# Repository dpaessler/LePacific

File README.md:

# LePacific

RIAA MM JFET Phono Preamplifier based on the design found here:

http://diyaudioprojects.com/Solid/JFET-Phono-Preamplifier-Kit/diy-jfet-riaa-phono-preamp.html

An additional EAGLE library is used for the JFET, which can be found here:

http://www.diymodules.org/eagle-show-library?type=usr&id=3220&part=toshiba-jfet.lbr

The coupling capacitors have to be added separately, they don't fit on the board. I used a matched pair
of NOS russian military 2.2uF 250V PIO capacitors K75-10.

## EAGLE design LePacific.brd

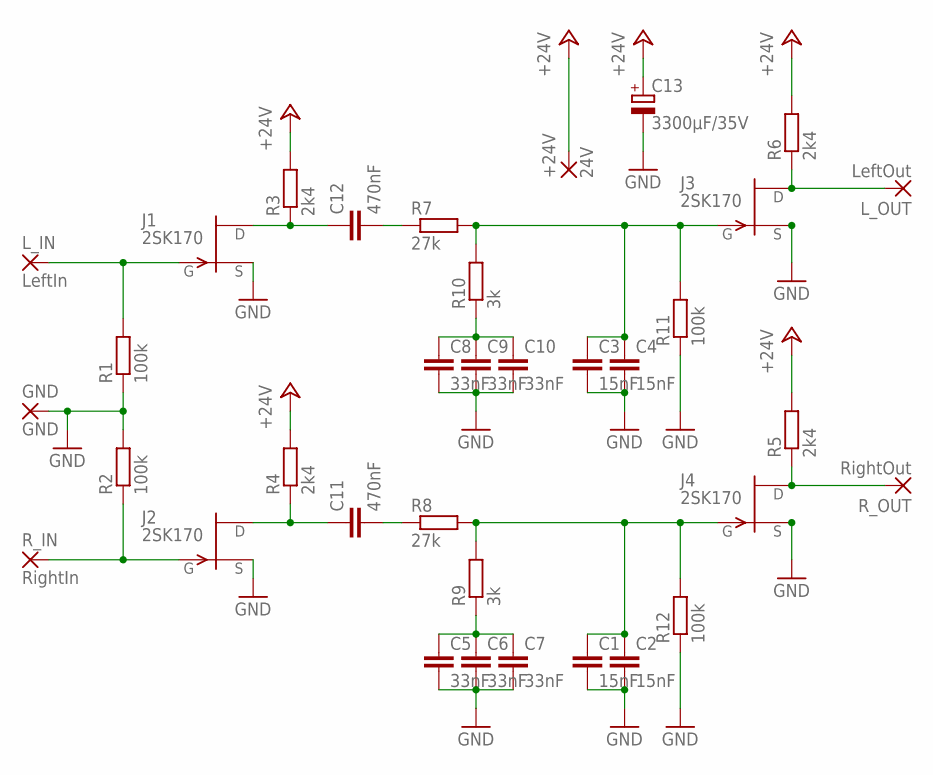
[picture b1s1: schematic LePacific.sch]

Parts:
+24V: 24V; 2,54/0,8
C1, C2, C3, C4: 15nF; C150-054X183
C5, C6, C7, C8, C9, C10: 33nF; C225-062X268
C11, C12: 470nF; C225-108X268
C13: 3300µF/35V; E7,5-16
GND: GND; 2,54/0,8
J1, J2, J3, J4: 2SK170; TO-92
L_IN: LeftIn; 2,54/0,8
L_OUT: LeftOut; 2,54/0,8
R1, R2, R11, R12: 100k; 0207/10
R3, R4, R5, R6: 2k4; 0207/10
R7, R8: 27k; 0207/10
R9, R10: 3k; 0207/10
R_IN: RightIn; 2,54/0,8
R_OUT: RightOut; 2,54/0,8

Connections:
+24V: +24V.1, C13.+, R3.2, R4.2, R5.2, R6.2
GND: C1.2, C2.2, C3.2, C4.2, C5.2, C6.2, C7.2, C8.2, C9.2, C10.2, C13.-, GND.1, J1.3 (S), J2.3 (S), J3.3 (S), J4.3 (S), R1.1, R2.2, R11.1, R12.1
unnamed: J1.2 (G), L_IN.1, R1.2
unnamed: J2.2 (G), R2.1, R_IN.1
unnamed: C11.2, R8.1
unnamed: C11.1, J2.1 (D), R4.1
unnamed: C12.1, J1.1 (D), R3.1
unnamed: C12.2, R7.1
unnamed: C3.1, C4.1, J3.2 (G), R7.2, R10.2, R11.2
unnamed: C1.1, C2.1, J4.2 (G), R8.2, R9.2, R12.2
unnamed: J3.1 (D), L_OUT.1, R6.1
unnamed: J4.1 (D), R5.1, R_OUT.1
unnamed: C5.1, C6.1, C7.1, R9.1
unnamed: C8.1, C9.1, C10.1, R10.1

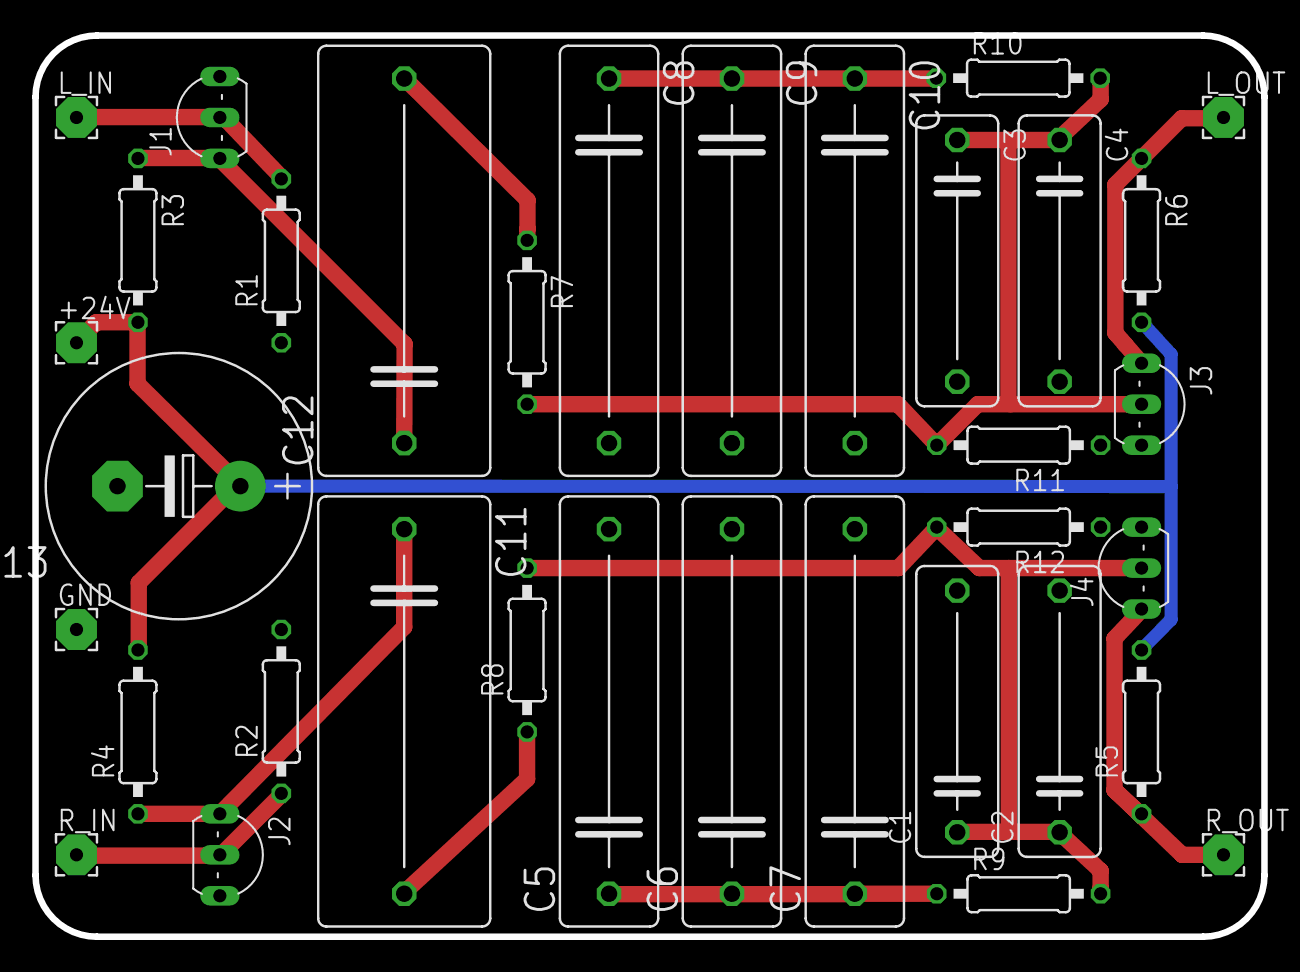
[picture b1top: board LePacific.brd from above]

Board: 2 copper layers, 76.2 x 55.9 mm, 35 parts (0 on the bottom side), 14 nets.

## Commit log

2016-12-03 added EAGLE files
